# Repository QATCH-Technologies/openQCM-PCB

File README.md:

# openQCM-PCB
KiCad project of the QATCH openQCM main circuit PCB (requires Teensy 4.1)

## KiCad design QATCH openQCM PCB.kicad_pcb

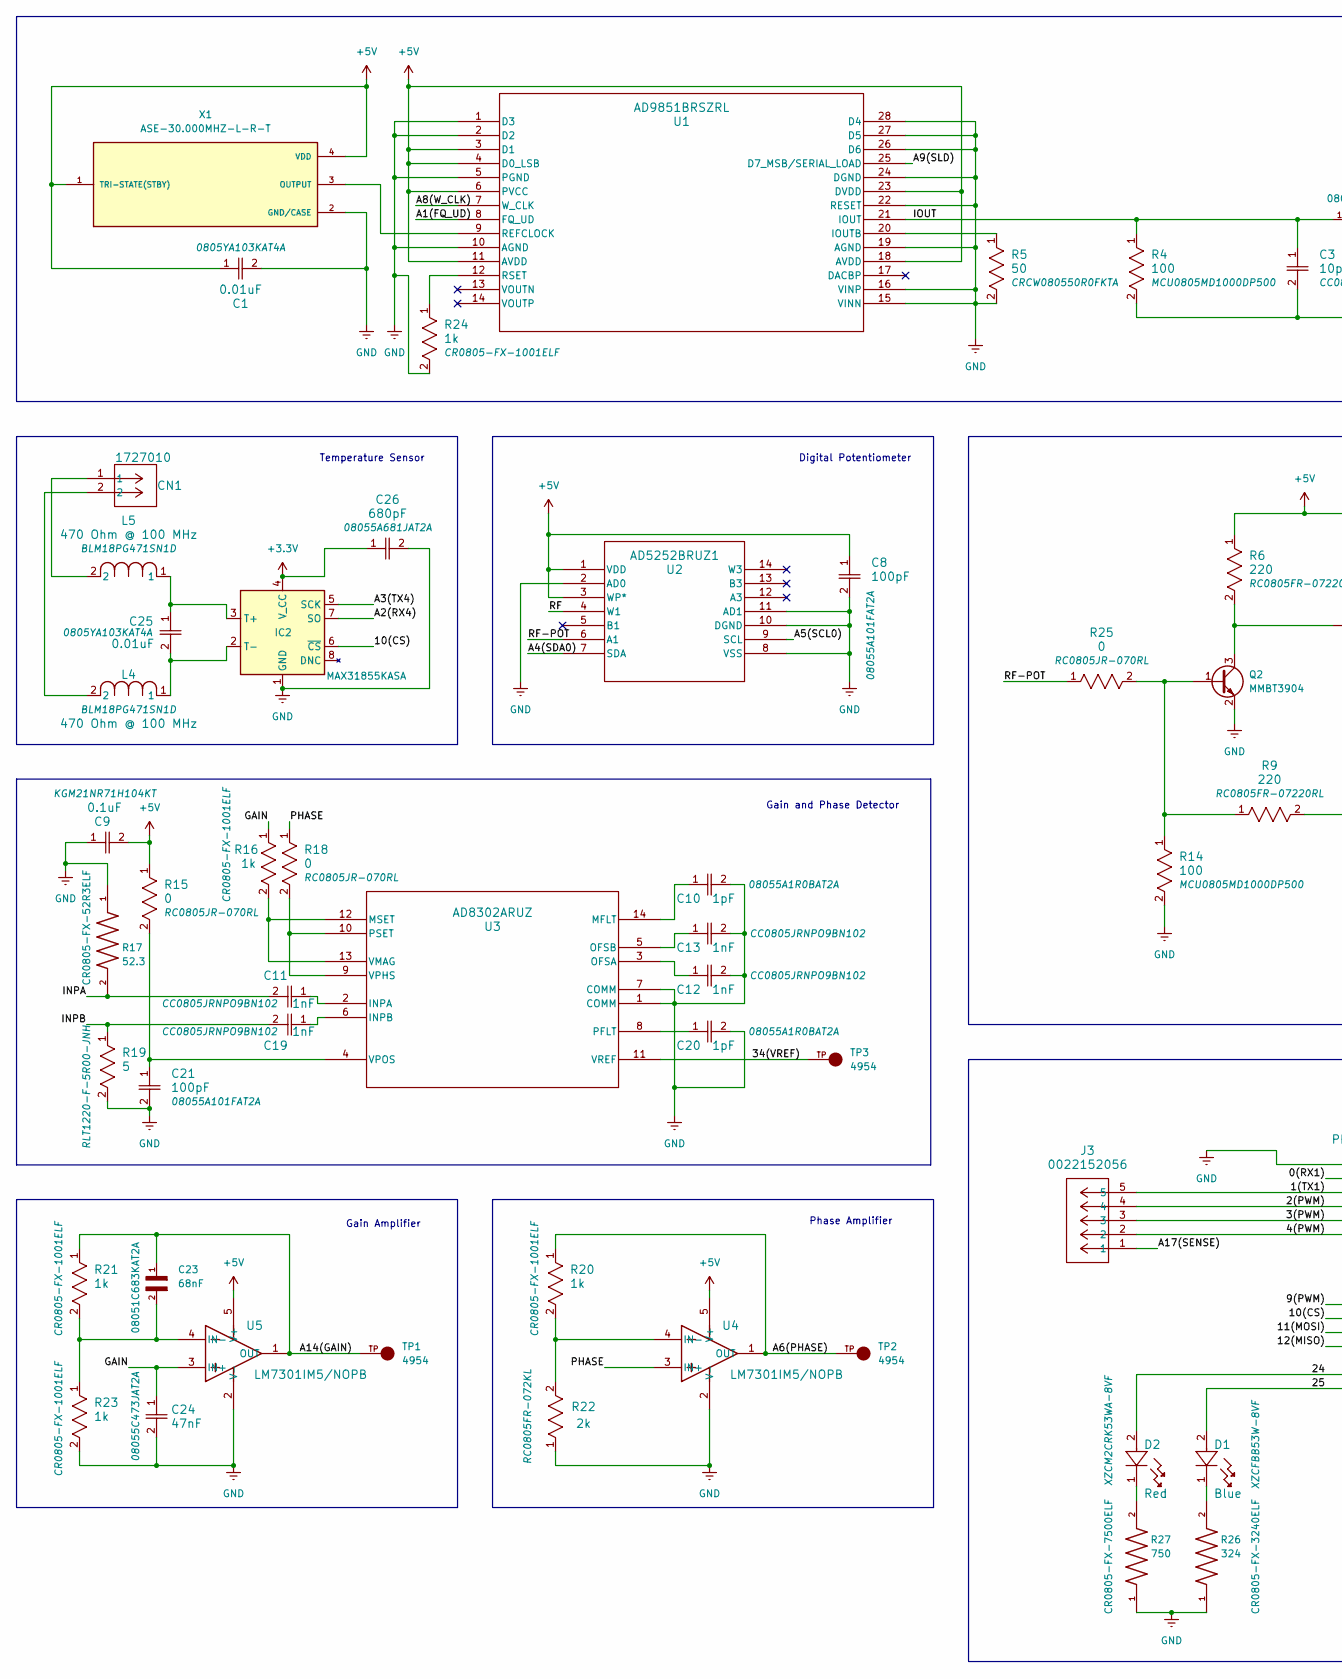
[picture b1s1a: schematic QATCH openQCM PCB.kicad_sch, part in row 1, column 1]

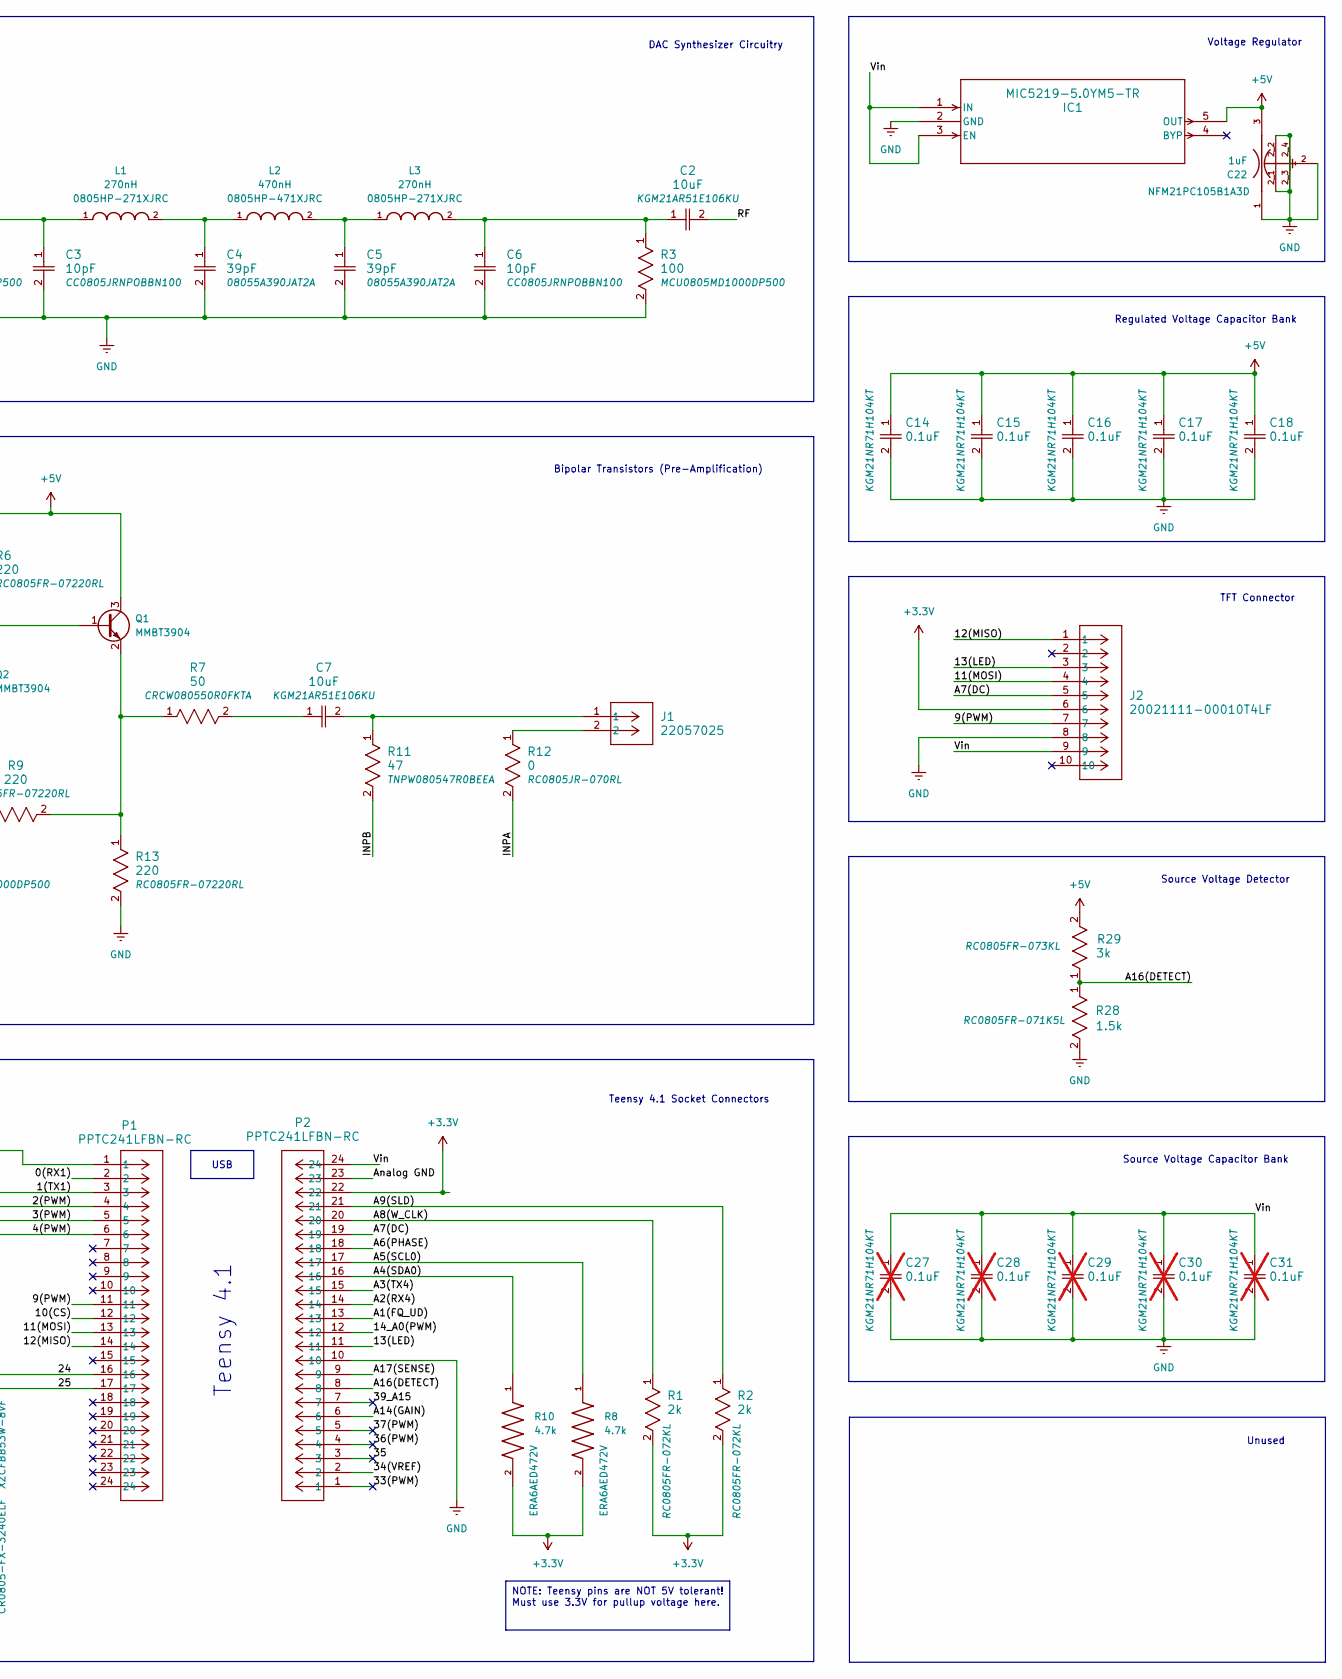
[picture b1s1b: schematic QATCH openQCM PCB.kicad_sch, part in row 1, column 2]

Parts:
C1, C25: 0.01uF; CAP_08051A0R8CAT2A_AVX
C2, C7: 10uF; CAP_KGM21_KAV
C3, C6: 10pF; CAP_CC0805_YAG
C4, C5: 39pF; CAP_0805J_AVX
C8, C21: 100pF; CAP_0805J_AVX
C9, C14, C15, C16, C17, C18: 0.1uF; CAP_KGM21_KAV
C10, C20: 1pF; CAP_0805J_AVX
C11, C12, C13, C19: 1nF; CAP_CC0805_YAG
C22: 1uF; FIL_NFM21PC105B1A3D; PARTREV N/A
C23: 68nF; CAPC2012X140N
C24: 47nF; 0805_AVX
C26: 680pF; CAP_0805J_AVX
C27, C28, C29, C30, C31: 0.1uF; CAP_KGM21_KAV; not fitted
CN1: 1727010; CONN_1727010
D1: Blue; LED_SMD_XZCM_1P6X0P8_SLD
D2: Red; LED_SMD_XZCM_1P6X0P8_SLD
IC1: MIC5219-5.0YM5-TR; SOT-23-5_M5_MCH
IC2: MAX31855KASA; SOIC-8_3.9x4.9mm_P1.27mm
J1: 22057025; CON_22057025_MOL
J2: 20021111-00010T4LF; CONN_MINITEK_2X5_HDR
J3: 0022152056; CON_22152056_MOL
L1, L3: 270nH; INDC2015X152N
L2: 470nH; INDC2015X152N
L4, L5: 470 Ohm @ 100 MHz; IND_BLM18_0603_MUR
P1, P2: PPTC241LFBN-RC; CONN24_PPTC241LFBN-RC_SUL
Q1, Q2: MMBT3904; SOT-23
R1, R2, R22: 2k; RC0805N_YAG
R3, R4, R14: 100; MCU0805-AT_VIS
R5, R7: 50; RES_RC0805_YAG
R6, R9, R13: 220; RES_RC0805_YAG
R8, R10: 4.7k; RES_ERA6AED472V; PARTREV 3/1/2020
R11: 47; RES_TNPW0805_VIS
R12, R15, R18, R25: 0; RC0805N_YAG
R16, R20, R21, R23, R24: 1k; BO_CR0805
R17: 52.3; RESC2012X60N; DigiKey_Part_Number 118-CR0805-FX-52R3ELFTR-ND
R19: 5; RES_ERA6AED472V
R26: 324; RESC2012X60N
R27: 750; RESC2012X60N
R28: 1.5k; RC0805N_YAG
R29: 3k; RC0805N_YAG
TP1, TP2, TP3: 4954; KEYSTONE_4954; PARTREV B
U1: AD9851BRSZRL; RS_28_ADI
U2: AD5252BRUZ1; RU_14_ADI
U3: AD8302ARUZ; RU_14_ADI
U4, U5: LM7301IM5/NOPB; SOT95P280X145-5N
X1: ASE-30.000MHZ-L-R-T; XTAL_ASE-30.000MHZ-L-R-T; PARTREV 02-18-22

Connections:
+3.3V: C26.1, IC2.4 (V_CC), J2.6, P2.22, R1.2, R2.2, R8.2, R10.2
+5V: C1.1, C8.1, C9.2, C14.1, C15.1, C16.1, C17.1, C18.1, C22.3, IC1.5 (OUT), Q1.3 (C), R6.1, R15.1, R29.2, U1.3 (D1), U1.4 (D0_LSB), U1.6 (PVCC), U1.11 (AVDD), U1.18 (AVDD), U1.23 (DVDD), U2.1 (VDD), U2.3 (WP*), U4.5 (V+), U5.5 (V+), X1.1 (TRI-STATE(STBY)), X1.4 (VDD)
/0(RX1): P1.2
/1(TX1): J3.5, P1.3
/2(PWM): J3.4, P1.4
/3(PWM): J3.3, P1.5
/4(PWM): J3.2, P1.6
/9(PWM): J2.7, P1.11
/10(CS): IC2.6 (~CS), P1.12
/11(MOSI): J2.4, P1.13
/12(MISO): J2.1, P1.14
/13(LED): J2.3, P2.11
/14_A0(PWM): P2.12
/24: D2.2, P1.16
/25: D1.2, P1.17
/33(PWM): P2.1
/34(VREF): P2.2, TP3.TP, U3.11 (VREF)
/35: P2.3
/36(PWM): P2.4
/37(PWM): P2.5
/39_A15: P2.7
/A1(FQ_UD): P2.13, U1.8 (FQ_UD)
/A2(RX4): IC2.7 (SO), P2.14
/A3(TX4): IC2.5 (SCK), P2.15
/A4(SDA0): P2.16, R10.1, U2.7 (SDA)
/A5(SCL0): P2.17, R8.1, U2.9 (SCL)
/A6(PHASE): P2.18, R20.1, TP2.TP, U4.1 (OUT)
/A7(DC): J2.5, P2.19
/A8(W_CLK): P2.20, R1.1, U1.7 (W_CLK)
/A9(SLD): P2.21, R2.1, U1.25 (D7_MSB/SERIAL_LOAD)
/A14(GAIN): C23.1, P2.6, R21.1, TP1.TP, U5.1 (OUT)
/A16(DETECT): P2.8, R28.1, R29.1
/A17(SENSE): J3.1, P2.9
/Analog GND: P2.23
/GAIN: C24.1, R16.1, U5.3 (IN+)
/INPA: C11.2, R12.2, R17.2
/INPB: C19.2, R11.2, R19.1
/IOUT: C3.1, L1.1, R4.1, U1.21 (IOUT)
/PHASE: R18.1, U4.3 (IN+)
/RF: C2.2, U2.4 (W1)
/RF-POT: R25.1, U2.6 (A1)
/Vin: C27.1, C28.1, C29.1, C30.1, C31.1, IC1.1 (IN), IC1.3 (EN), J2.9, P2.24
GND: C1.2, C3.2, C4.2, C5.2, C6.2, C8.2, C9.1, C10.2, C12.2, C13.2, C14.2, C15.2, C16.2, C17.2, C18.2, C20.2, C21.2, C22.1, C22.2, C22.2_1, C22.2_2, C22.2_3, C22.2_4, C24.2, C26.2, C27.2, C28.2, C29.2, C30.2, C31.2, IC1.2 (GND), IC2.1 (GND), J2.8, P1.1, P2.10, Q2.2 (E), R3.2, R4.2, R5.2, R13.2, R14.2, R17.1, R19.2, R22.1, R23.2, R24.2, R26.1, R27.1, R28.2, U1.1 (D3), U1.2 (D2), U1.5 (PGND), U1.10 (AGND), U1.15 (VINN), U1.16 (VINP), U1.19 (AGND), U1.22 (RESET), U1.24 (DGND), U1.26 (D6), U1.27 (D5), U1.28 (D4), U2.2 (AD0), U2.8 (VSS), U2.10 (DGND), U2.11 (AD1), U3.1 (COMM), U3.7 (COMM), U4.2 (V-), U5.2 (V-), X1.2 (GND/CASE)
unnamed: C2.1, C6.1, L3.2, R3.1
unnamed: C4.1, L1.2, L2.1
unnamed: C5.1, L2.2, L3.1
unnamed: C7.1, R7.2
unnamed: C7.2, J1.1, R11.1
unnamed: CN1.1, L5.2
unnamed: CN1.2, L4.2
unnamed: D1.1, R26.2
unnamed: D2.1, R27.2
unnamed: C25.1, IC2.3 (T+), L5.1
unnamed: C25.2, IC2.2 (T-), L4.1
unnamed: J1.2, R12.1
unnamed: Q1.1 (B), Q2.3 (C), R6.2
unnamed: Q1.2 (E), R7.1, R9.2, R13.1
unnamed: Q2.1 (B), R9.1, R14.1, R25.2
unnamed: R5.1, U1.20 (IOUTB)
unnamed: U1.9 (REFCLOCK), X1.3 (OUTPUT)
unnamed: R24.1, U1.12 (RSET)
unnamed: C11.1, U3.2 (INPA)
unnamed: C19.1, U3.6 (INPB)
unnamed: C10.1, U3.14 (MFLT)
unnamed: R16.2, U3.12 (MSET), U3.13 (VMAG)
unnamed: C12.1, U3.3 (OFSA)
unnamed: C13.1, U3.5 (OFSB)
unnamed: C20.1, U3.8 (PFLT)
unnamed: R18.2, U3.9 (VPHS), U3.10 (PSET)
unnamed: C21.1, R15.2, U3.4 (VPOS)
unnamed: R20.2, R22.2, U4.4 (IN-)
unnamed: C23.2, R21.2, R23.1, U5.4 (IN-)

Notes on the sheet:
USB
NOTE: Teensy pins are NOT 5V tolerant! Must use 3.3V for pullup voltage here.
Source Voltage Capacitor Bank
Digital Potentiometer
Phase Amplifier
Gain and Phase Detector
Voltage Regulator
Gain Amplifier
Teensy 4.1 Socket Connectors
TFT Connector
Source Voltage Detector
Temperature Sensor
Teensy 4.1
Bipolar Transistors (Pre-Amplification)
Regulated Voltage Capacitor Bank
Unused
DAC Synthesizer Circuitry

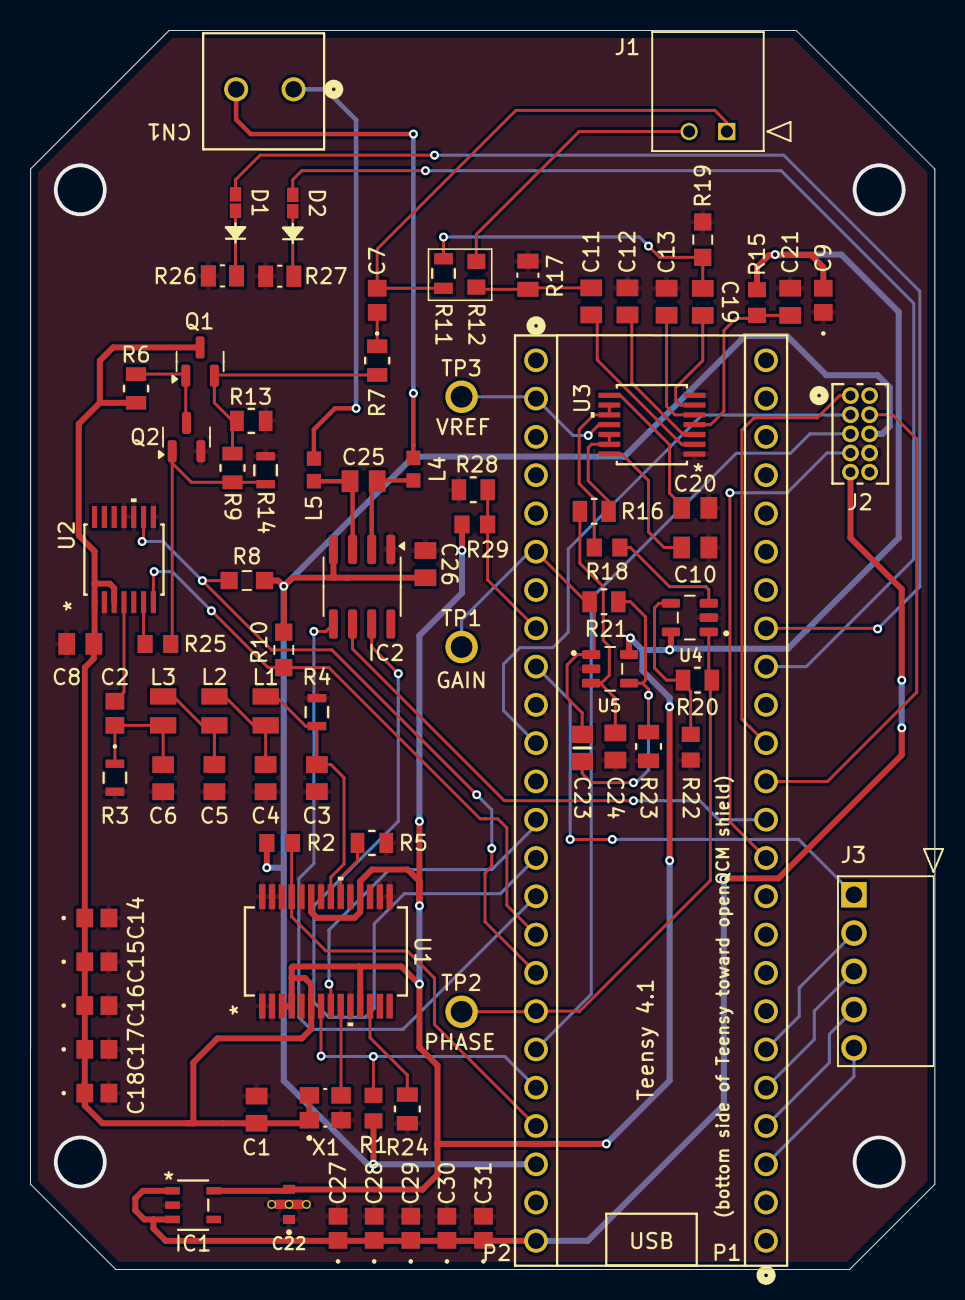
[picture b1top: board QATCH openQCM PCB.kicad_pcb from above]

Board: 2 copper layers, 60.0 x 82.2 mm, 86 parts (0 on the bottom side), 64 nets.

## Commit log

2024-05-16 Initial commit of KiCad project to GitHub
2024-05-21 Allow BOM files in repo
2025-04-10 Committing local changes, adding cap bank and fix 5V pullups
